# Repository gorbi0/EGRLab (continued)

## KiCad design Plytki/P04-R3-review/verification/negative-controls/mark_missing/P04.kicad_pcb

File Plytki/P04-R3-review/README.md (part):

# P04 SAFE — R3, schemat w formacie S1

*5.10.2026. Pakiet na kopii łańcucha schematu `P04-R2.2-review/src` według `Plytki/Format-S1/zadania/ZADANIE-P04-S1.md` (decyzja użytkownika 5.10.2026: wariant pełny, P04 na 6. poziomie, klasa L). Zamknięty pakiet R2.2 bez zmian.*

**Status (5.10.2026): schemat R3 i PCB (sesja lokalna, gałąź `p04-r3-pcb`) do recenzji; paczka zamówieniowa `Plytki/P04-PCB-R3-zamowienie`.** Sekcja „PCB” niżej. Sprzętu nie zmontowano ani nie zmierzono.

Obwód R2.2 zostaje: watchdog CD74HC123 (U1), zatrzask ARM 74HC74 (U3), regeneracja SAFE_N przez 74HC14 (U2), bramki 74HC08 (U4–U7), bufory 74LVC125AD z Ioff i podwójnymi pulldownami (U8–U10), nadzorca MCP100-300 (U11), otwarte kolektory Q1–Q3 na SAFE_N, druga droga watchdoga SAFE_WD, R17 10 kΩ pod reset z P03. Zmieniają się złącza do innych płytek, punkty pomiarowe, typy części i wymiar. `verify_s1.py` sprawdza na eksportowanej netliście, że poza złączami J1–J8 i polami TP każdy pin ma tę samą sieć i wartość co w R2.2 (`reference/P04-R2.2.xml`), z dwiema jawnymi zmianami nazw.

## Zmiany R2.2 → R3

| Punkt | R2.2 | R3 |
|---|---|---|
| Płytka | 160 × 120 mm, 4 otwory, samodzielna | klasa L 160 × 100 mm, poziom 6 (sloty S1–S3), 12 otworów M3, dystanse 20 mm |
| Złącza | J1 LV04 i J2 SAFE (pigtaile z kotwami), J3–J6 IDC, J7 PG i J8 PANELSAFE (Mini-Fit) | **J_BP1** IDC 2×8 (S1, x = 26,5), **J_BP2** i **J_BP3** IDC 2×10 (S2 x = 80,0, S3 x = 133,5), kątowe obudowane, wszystkie nieparzyste GND, przez P12 |
| Nazwy sieci | SUP_N (J2.15), PG_3V3 (J7.1) | **SUP_N_OUT**, **P04_3V3** — nazwy z P12 (P03 R6 J_BP3.12, P02 R4 J_BP.15) |
| Drugi koniec PG/SAFE_N | P01 J5 | P02 R4 (Q7, zwora PG) przez P12; P07 łączy się z SAFE_N po nazwie |
| Punkty pomiarowe | TP1–TP15 | **J_SV1** 1×13, **J_SV2** 1×7, **J_SV3** 1×7 na krawędzi B; 19 kołków przez R43–R61 przy węzłach (mapa w `docs/ODBIOR.md`) |
| Rezystory | MFR-25 THT leżące | nowe **SMD 1206** RC1206FR-07… (rejestr nie ma zapasu tych wartości) |
| Kondensatory | K104K15 100 n THT, K102J15 1 n, EEUFR1H100, 2 × MKS2 63 V | 100 n **X7R 1206**; posiadane: C1 MKS2 1 µF / 100 V, C3 EEU-EB1J100SH, C18 C320C102J1G5TA; C2 nowy MKS2 jak w R2.2 |
| U8–U10 | SO14 na adapterach Kamami, C15–C17 na adapterach | **SOIC-14 lutowane wprost** (S1 §9); C15–C17 na płytce jako druga 100 n przy U8–U10 |
| Arkusze | 6 (w tym `CON`) | 7: `CON` → **`ZLACZA`** (nazwa zarezerwowana w Windows, `docs/CHMURA.md`), nowy **`SERWIS`** |

## Pinout J_BP (pełny: `docs/J_BP.csv`, kierunki widziane z P04)

| Pin | J_BP1 (S1) | J_BP2 (S2) | J_BP3 (S3) |
|---|---|---|---|
| 2 | PANEL_3V3 → P11 | MOTOR_PERMIT → P07 | SENSOR_ENABLE ← P03 |
| 4 | MECH_OK ← P11 | PWM_OUT → P07 | CORE_LINK ← P03 |
| 6 | STOP_NC_OUT ← P11 | ARM_CLK → P07 | HW_ARMED → P03 |
| 8 | ARM_CONTACT ← P11 | DRIVE_OK ← P07 | 5V_SYS (tylko kołek) |
| 10 | SENSOR_PERMIT → P08 | 3V3_IO (zasilanie) | 3V3_IO (zasilanie) |
| 12 | SENSOR_OK ← P08 | PSU_OK ← P02 | SUP_N_OUT ← P03 |
| 14 | TEST_KEY ← P11 | P04_3V3 → P02 | PWM ← P03 |
| 16 | DAQ_OK ← P05 | SAFE_N (węzeł OC) | HEARTBEAT ← P03 |
| 18 | — | PG_LINK (pętla P02) | MCU_ARM ← P03 |
| 20 | — | PG_SEND (pętla P02) | INTERLOCK → P03 |

Nieparzyste: GND. Te same numery pinów co u partnera tam, gdzie się dało: J_BP1 2/4/6/8/14 = P11 J_P12, J_BP2 12/16/18 = P02 R4 J_BP, J_BP3 12–20 = P03 R6 J_BP3 — taśmy na P12 idą wtedy prosto. Sieci do P07 (DRIVE) i P08 (SENSOR) mają nazwy z R2.2 J3/J4 (i z P08 R1 W2); **P07 jeszcze nie istnieje — te sieci czekają na P07**.

## Kontrole

`python src/run_schematic.py` (w chmurze `scripts/egrlab-docker python3 src/run_schematic.py`, ok. 20 s): schemat, tabele, ERC, netlista, cztery zestawy kontroli, PDF, `verification/QA.md`, manifest.

- ERC **0** na 7 arkuszach; netlista **397/397** pinów zgodnych z `parts.py`, 100 części, 95 sieci.
- `verify_electrical.py` (kontrole R2.2 z pinami przeniesionymi na J_BP): **22/22**, mutacje **16/16** — m.in. pełne tabele prawdy INTERLOCK / SAFE_N / HW_ARMED / MOTOR_PERMIT / PWM_OUT / SENSOR_PERMIT (131 072 wierszy), druga droga watchdoga bez Q1, sekwencje ARM bez samoczynnego uzbrojenia, SAFE_N tylko z jednym podciąganiem i kolektorami (rezystor kołka serwisowego pominięty jawnie), 3V3 wychodzi z płytki tylko przez R38/R39/R40.
- `verify_values.py`: **10/10**, mutacje **24/24** (wartości i MPN S1, rogi rezystorów panelu i SAFE_N).
- `verify_reset.py` z mapą części **P03 R6**: **7/7**, mutacje **4/4** (R17 10 kΩ, VIL/VIH na U9.5, SUP_N_OUT na J_BP3.12 po obu stronach).
- `verify_s1.py` (kontrakt S1 i P12, niezależny od generatora): **34/34**, mutacje **42/42** wykryte przez kontrolę docelową, próba zerowa czysta. Sprawdza m.in.: pinout i footprint każdego J_BP; nieparzyste GND; każda sieć dawnych J1–J8 na J_BP dokładnie raz (3V3_IO dwa razy); te same piny co partner; **każda z 19 sieci „czeka na P04” w `reference/P12-kontrakty.json` kończy się na P04 dokładnie raz i po dołączeniu P04 ma jeden nadajnik (albo pętlę)**; brak obcych nazw; nazwy DRIVE/SENSOR jak w R2.2 i P08 R1; zgodność `J_BP.csv` i `SERWIS.csv` z netlistą; listwy ≤ 13 kołków z GND na końcach, rezystor przy węźle w swojej klasie, SAFE_N i ARM_BUTTON_N tylko obok GND, szyny tylko obok GND lub szyn; pokrycie TP1–TP15 z R2.2; obudowy S1; obwód R2.2 bez zmian.
- kicad-cli wypisuje „schemat posiada błędy numeracji” — oznaczenia `J_BP1…3`, `J_SV1…3` (nazwy formatu S1); ERC tego nie zgłasza.

## Decyzje (sporne oznaczone)

1. **Trzy J_BP zamiast dwóch z budżetu S1 §8:** 25 sygnałów (19 czekających na P04 w P12 + 6 do P07/P08) i zasilanie nie mieszczą się w 2 × 10 parzystych pinach bez wyjątków od GND na nieparzystych; klasa L ma trzy sloty. J_BP1 jako 2×8 (osiem sygnałów).
2. **Sporne — SAFE_N w `J_BP.csv` jako `in`:** P04 ma podciąganie R4 i własne kolektory Q1–Q3, ale dla kontraktu P12 nadajnikiem jest P02 R4 (`out`); dwa `out` kontrola P12 uznałaby za konflikt. Uwaga w kolumnie `uwagi`.
3. **Sporne — U8–U10 SOIC wprost, bez adapterów:** S1 §9 dopuszcza adaptery tylko tam, gdzie jest miejsce; SOIC na płytce z fabryki jest prostszy i niższy (tak samo P06 R2). Adaptery z przydziału P04 zostają w rejestrze. C15–C17 przeniesione na płytkę, żeby obwód był identyczny z R2.2 — mogą zostać DNP.
4. **5V_SYS na jednym pinie (J_BP3.8), tylko do kołka J_SV3.2** — jak J1.1 → TP13 w R2.2; P04 nie pobiera 5 V, więc reguła „5V_SYS na ≥ 2 pinach” (S1 §5, dla zasilania) nie ma tu zastosowania.
5. **3V3_IO na dwóch pinach (J_BP2.10, J_BP3.10):** pobór kilka–kilkanaście mA, ale drugi pin daje zapas styku i masę obok.
6. **Klasy rezystorów kołków:** 1 kΩ szyny i węzły napędzane bramką; 10 kΩ węzły pasywne SAFE_N (R4 10k / R5 100k) i ARM_BUTTON_N (R2 10k). **Wyjątek Q1_B 1 kΩ:** próba E21 zwiera kołek do GND i musi zatkać Q1 (z 10 kΩ baza zostaje na ok. 1,57 V, z 1 kΩ ok. 0,30 V). **SAFE_N i ARM_BUTTON_N stoją tylko między kołkami GND:** zsunięta sonda zwierająca je z szyną podniosłaby SAFE_N mimo otwartego STOP albo dała zbocze ARM.
7. **Posiadane ostatnie sztuki z rejestru:** C1 MKS2 1 µF / 100 V (5 %), C3 EEU-EB1J100SH, C18 C320C102J1G5TA — bilans w `docs/ZAKUPY.md`. C2 zostaje foliowy (nowy, jak w R2.2), bo filtr ARM i tak wymaga kwalifikacji przycisku.

## PCB (5.10.2026, sesja lokalna; `src/run_release.py`, KiCad 10.0.6 w Dockerze)

| Kontrola | Wynik | Raport |
|---|---|---|
| DRC świeży, wszystkie poziomy, z parity | 0 niepołączonych, 0 niezgodności ze schematem, 0 innych naruszeń; 6 × `lib_footprint_mismatch` (J_BP1–3, J_SV1–3: nadruk przycięty przez `silkscreen.py`, pola równe bibliotece — przyjęte jawnie) | `verification/drc.json` |
| Kontrole PCB (`verify_pcb.py`) | 31/31 | `verification/pcb-checks.json`, `QA-PCB.md` |
| Próby ujemne PCB | 33/33 z próbą zerową | `verification/negative-controls.json` |
| Otwory M3 i strefy Ø7 | 12 NPTH 3,2 mm w punktach S1, bez miedzi i części w Ø7 | `pcb-checks.json` |
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
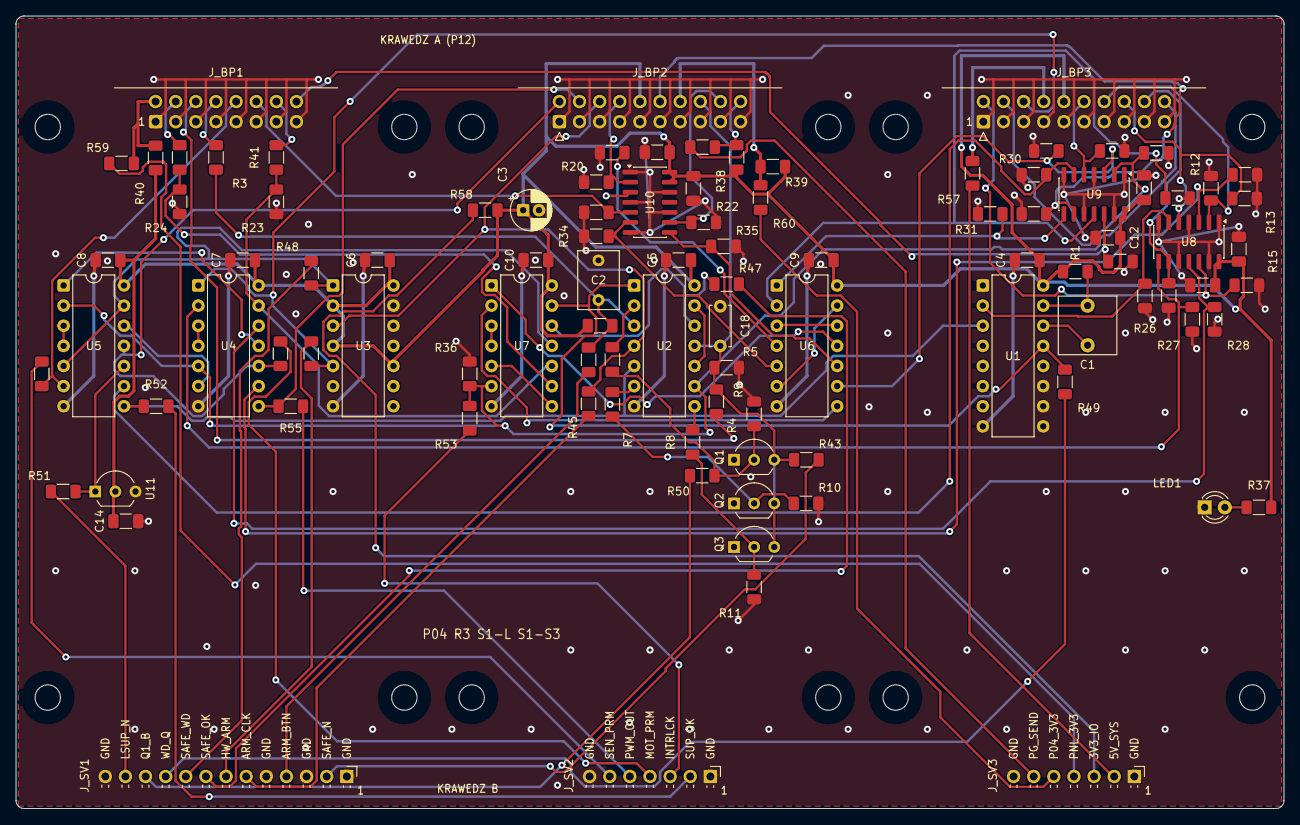
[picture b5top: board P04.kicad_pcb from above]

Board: 2 copper layers, 160.0 x 100.0 mm, 112 parts (0 on the bottom side), 86 nets.

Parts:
C1: 1u; C_WIMA_MKS2_1u100V_L7.2_W7.2_P5
C2: 1u; C_Rect_L7.2mm_W5.0mm_P5.00mm
C3: 10u; CP_Radial_D5.0mm_P2.00mm
C4, C5, C6, C7, C8, C9, C10, C11, C12, C13, C14, C15, C16, C17: 100n; C_1206_3216Metric_Pad1.33x1.80mm_HandSolder
C18: 1n; C_Disc_D5.0mm_W2.5mm_P5.00mm
H1, H2, H3, H4, H5, H6, H7, H8, H9, H10, H11, H12: M3 NPTH
J_BP1: J_BP1; IDC-Header_2x08_P2.54mm_Horizontal
J_BP2: J_BP2; IDC-Header_2x10_P2.54mm_Horizontal
J_BP3: J_BP3; IDC-Header_2x10_P2.54mm_Horizontal
J_SV1: J_SV1 SERWIS 1x13; PinHeader_1x13_P2.54mm_Horizontal
J_SV2: J_SV2 SERWIS 1x7; PinHeader_1x07_P2.54mm_Horizontal
J_SV3: J_SV3 SERWIS 1x7; PinHeader_1x07_P2.54mm_Horizontal
LED1: POWER; LED_D3.0mm
Q1, Q2, Q3: 2N3904; TO-92_Inline_Wide
R1: 220K; R_1206_3216Metric_Pad1.30x1.75mm_HandSolder
R2, R4, R6, R7, R8, R12, R13, R14, R15, R16, R17, R18, R19, R20, R21, R22, R23, R24, R25, R29, R31, R32, R33, R34, R35, R36, R43, R44: 10K; R_1206_3216Metric_Pad1.30x1.75mm_HandSolder
R3, R37, R38, R39, R41, R42, R45, R46, R47, R48, R49, R50, R51, R52, R53, R54, R55, R56, R57, R58, R59, R60, R61: 1K; R_1206_3216Metric_Pad1.30x1.75mm_HandSolder
R5, R9, R10, R11, R28, R30: 100K; R_1206_3216Metric_Pad1.30x1.75mm_HandSolder
R26, R27: 47K; R_1206_3216Metric_Pad1.30x1.75mm_HandSolder
R40: 100R; R_1206_3216Metric_Pad1.30x1.75mm_HandSolder
U1: CD74HC123E; DIP-16_W7.62mm
U2: SN74HC14N; DIP-14_W7.62mm
U3: SN74HC74N; DIP-14_W7.62mm
U4, U5, U6, U7: SN74HC08N; DIP-14_W7.62mm
U8, U9, U10: 74LVC125AD; SOIC-14_3.9x8.7mm_P1.27mm
U11: MCP100-300DI/TO; TO-92_Inline_Wide

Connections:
3V3_IO: C3.1, C4.1, C5.1, C6.1, C7.1, C8.1, C9.1, C10.1, C11.1, C12.1, C13.1, C14.1, C15.1, C16.1, C17.1, J_BP2.10, J_BP3.10, R1.1, R2.1, R37.1, R38.1, R39.1, R40.1, R58.1, U1.16, U2.14, U3.2, U3.4, U3.10, U3.14, U4.14, U5.14, U6.14, U7.14, U8.14, U9.14, U10.13, U10.14, U11.2
5V_SYS: J_BP3.8, R57.1
/ILK/MECH_KEY: U7.5, U7.8
/ILK/MECH_OK_P04: R24.1, R42.2, U7.9
/ILK/MODULES_OK: U7.3, U7.4
/ILK/OK_A: U6.3, U6.12
/ILK/OK_AB: U6.11, U7.1
/ILK/OK_B: U6.6, U6.13
/ILK/OK_C: U6.8, U7.2
/LED_PWR: LED1.2, R37.2
/OUT/ARM_BOTH: U4.3, U4.4
/OUT/MOTOR_REQ: U4.6, U5.12
/OUT/SENSOR_INTERLOCK: U5.3, U5.4
/OUT/SENSOR_KEY: U4.11, U5.1
/SERWIS/SRV_3V3_IO: J_SV3.3, R58.2
/SERWIS/SRV_5V_SYS: J_SV3.2, R57.2
/SERWIS/SRV_ARM_BUTTON_N: J_SV1.4, R44.2
/SERWIS/SRV_ARM_CLK: J_SV1.6, R45.2
/SERWIS/SRV_HW_ARMED: J_SV1.7, R46.2
/SERWIS/SRV_INTERLOCK: J_SV2.3, R53.2
/SERWIS/SRV_LOCAL_SUP_N: J_SV1.12, R51.2
/SERWIS/SRV_MOTOR_PERMIT: J_SV2.4, R54.2
/SERWIS/SRV_P04_3V3: J_SV3.5, R60.2
/SERWIS/SRV_PANEL_3V3: J_SV3.4, R59.2
/SERWIS/SRV_PG_SEND: J_SV3.6, R61.2
/SERWIS/SRV_PWM_OUT: J_SV2.5, R55.2
/SERWIS/SRV_Q1_B: J_SV1.11, R50.2
/SERWIS/SRV_SAFE_N: J_SV1.2, R43.2
/SERWIS/SRV_SAFE_OK: J_SV1.8, R47.2
/SERWIS/SRV_SAFE_WD: J_SV1.9, R48.2
/SERWIS/SRV_SENSOR_PERMIT: J_SV2.6, R56.2
/SERWIS/SRV_SUP_OK: J_SV2.2, R52.2
/SERWIS/SRV_WD_Q: J_SV1.10, R49.2
/WD/ILK_BAD: R8.1, U2.8
/WD/Q2_B: Q2.2, R7.2, R10.1
/WD/Q3_B: Q3.2, R8.2, R11.1
/WD/SAFE_OK_N: U2.10, U2.13
/WD/SUP_BAD: R7.1, U2.6
/WD/WD_BAD: R6.1, U2.2
/WD/WD_C: C1.2, U1.14
/WD/WD_RC: C1.1, R1.2, U1.15
ARM_BUTTON_N: C2.1, R2.2, R3.1, R44.1, U2.3
ARM_CLK: J_BP2.6, R45.1, U2.4, U3.3
ARM_CONTACT: J_BP1.8, R3.2
CORE_LINK: J_BP3.4, R16.1, U9.2
CORE_LINK_P04: R29.1, U6.9, U9.3
DAQ_OK: J_BP1.16, R19.1, U9.12
DAQ_OK_P04: R32.1, U6.2, U9.11
DRIVE_OK: J_BP2.8, R20.1, U10.2
DRIVE_OK_P04: R33.1, U6.4, U10.3
GND: C2.2, C3.2, C4.2, C5.2, C6.2, C7.2, C8.2, C9.2, C10.2, C11.2, C12.2, C13.2, C14.2, C15.2, C16.2, C17.2, C18.2, J_BP1.1, J_BP1.3, J_BP1.5, J_BP1.7, J_BP1.9, J_BP1.11, J_BP1.13, J_BP1.15, J_BP2.1, J_BP2.3, J_BP2.5, J_BP2.7, J_BP2.9, J_BP2.11, J_BP2.13, J_BP2.15, J_BP2.17, J_BP2.19, J_BP3.1, J_BP3.3, J_BP3.5, J_BP3.7, J_BP3.9, J_BP3.11, J_BP3.13, J_BP3.15, J_BP3.17, J_BP3.19, J_SV1.1, J_SV1.3, J_SV1.5, J_SV1.13, J_SV2.1, J_SV2.7, J_SV3.1, J_SV3.7, LED1.1, Q1.1, Q2.1, Q3.1, R5.2, R9.2, R10.2, R11.2, R12.2, R13.2, R14.2, R15.2, R16.2, R17.2, R18.2, R19.2, R20.2, R21.2, R22.2, R23.2, R24.2, R25.2, R26.2, R27.2, R28.2, R29.2, R30.2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
HEARTBEAT: J_BP3.16, R13.1, U8.5
HEARTBEAT_P04: R26.1, U1.2, U8.6
HW_ARMED: J_BP3.6, R46.1, U3.5, U4.1
INTERLOCK: J_BP3.20, R36.1, R53.1, U2.9, U4.5, U5.2, U7.6
LOCAL_SUP_N: R51.1, U5.10, U11.1
MCU_ARM: J_BP3.18, R14.1, U8.9
MCU_ARM_P04: R27.1, U4.2, U8.8
MECH_OK: J_BP1.4, R42.1
MOTOR_PERMIT: J_BP2.2, R54.1, U4.10, U5.11
P04_3V3: J_BP2.14, R39.2, R60.1
PANEL_3V3: J_BP1.2, R40.2, R59.1
PG_LINK: J_BP2.18, R22.1, U10.9
PG_LINK_P04: R35.1, U6.10, U10.8
PG_SEND: J_BP2.20, R38.2, R61.1
PSU_OK: J_BP2.12, R18.1, U9.9
PSU_OK_P04: R31.1, U6.1, U9.8
PWM: J_BP3.14, R12.1, U8.2
PWM_OUT: J_BP2.4, R55.1, U4.8
PWM_P04: R25.1, U4.9, U8.3
Q1_B: Q1.2, R6.2, R9.1, R50.1
SAFE_N: C18.1, J_BP2.16, Q1.3, Q2.3, Q3.3, R4.2, R5.1, R43.1, U2.11
SAFE_OK: R47.1, U2.12, U7.12
SAFE_WD: R48.1, U3.1, U5.5, U5.13, U7.11
SENSOR_ENABLE: J_BP3.2, R15.1, U8.12
SENSOR_ENABLE_P04: R28.1, U4.12, U8.11
SENSOR_OK: J_BP1.12, R21.1, U10.5
SENSOR_OK_P04: R34.1, U6.5, U10.6
SENSOR_PERMIT: J_BP1.10, R56.1, U5.6
STOP_NC_OUT: J_BP1.6, R4.1
SUP_N_OUT: J_BP3.12, R17.1, U9.5
SUP_N_P04: R30.1, U5.9, U9.6
SUP_OK: R52.1, U1.3, U2.5, U5.8
TEST_KEY: J_BP1.14, R41.1
TEST_KEY_P04: R23.1, R41.2, U4.13, U7.10
WD_Q: R49.1, U1.13, U2.1, U7.13

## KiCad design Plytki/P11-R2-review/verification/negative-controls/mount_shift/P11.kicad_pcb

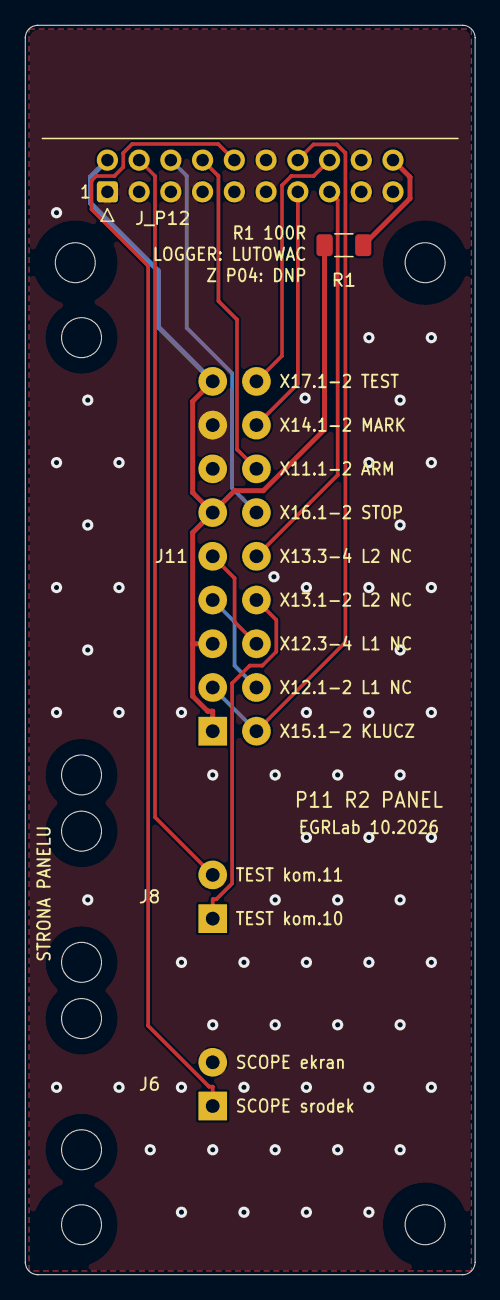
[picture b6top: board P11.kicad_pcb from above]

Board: 2 copper layers, 36.0 x 100.0 mm, 9 parts (0 on the bottom side), 14 nets.

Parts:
H1, H2, H3, H4: M3 NPTH
J6: SCOPE tail; FIELD_PAIR2
J8: TEST signal; FIELD_PAIR2
J11: CONTACTS; FIELD_CONTACT18
J_P12: IDC 2x10 katowe do P12; IDC-Header_2x10_P2.54mm_Horizontal
R1: 100R; R_1206_3216Metric_Pad1.30x1.75mm_HandSolder

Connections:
/3V3_IO: J_P12.20, R1.1
/CONTACTS/DIAG_L1_L2: J11.6, J11.9
/CONTACTS/ILK_L1_L2: J11.4, J11.7
/CONTACTS/LOOP_OUT: J8.1, J11.8
/N_J_SCOPE_HOT: J6.1, J_P12.10
ARM_CONTACT: J11.14, J_P12.8
GND: J6.2, J11.13, J11.15, J_P12.1, J_P12.3, J_P12.5, J_P12.7, J_P12.9, J_P12.11, J_P12.12, J_P12.17, J_P12.18, J_P12.19
LOGGER_CLEAR: J11.10, J_P12.15
MARK: J11.16, J_P12.13
MECH_OK: J8.2, J_P12.4
PANEL_3V3: J11.1, J11.5, J11.11, J11.17, J_P12.2, R1.2
STOP_NC_OUT: J11.12, J_P12.6
TEST_KEY: J11.2, J11.3, J_P12.14
TEST_PRESENT: J11.18, J_P12.16

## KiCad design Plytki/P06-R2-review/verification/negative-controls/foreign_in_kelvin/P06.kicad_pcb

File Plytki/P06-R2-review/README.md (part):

# P06 I-LOGGER — R2, schemat w formacie S1

*1.10.2026. Pakiet na kopii łańcucha `P06-R1-review/src` według `Plytki/Format-S1/zadania/ZADANIE-P06-S1.md` (decyzje użytkownika 1.10.2026: klasa 2/3, bocznik 2512 Kelvin, BYPASS na panelu, C3 220 µF). Zamknięty pakiet R1 bez zmian.*

**Status: schemat R2 po przeglądzie lokalnym, PCB R2 po recenzji niezależnej i poprawkach (2.10)** — sekcja „PCB” niżej. Sprzętu nie zmontowano ani nie zmierzono.

Obwód R1 zostaje: INA240A2 z filtrem R1/R2 10 Ω, dzielnik R3/R4 1:2, MCP6022, MCP3201, nadzorcy MCP120, bufory 74LVC125 z Ioff, logika LOGGER_CURRENT_OK, R21 (prąd zwilżania styku statusu BYPASS). Zmieniają się złącza do innych płytek, bocznik, punkty pomiarowe i typy części. `verify_s1.py` sprawdza na eksportowanej netliście, że poza J1/J2, bocznikiem i polami testowymi każdy pin obwodu R1 ma tę samą sieć co w R1 (`reference/P06-R1.xml`).

## Zmiany R1 → R2

| Punkt | R1 | R2 |
|---|---|---|
| Płytka | 120 × 100 mm, 2 × 70 µm, samodzielnie mocowana | klasa 2/3, 106,5 × 100 mm, sloty S1–S2 poziomu 4, dystanse 20 mm, 35 µm |
| Zasilanie i ILOG | J1 LV06 (Mini-Fit 4p, 200 mm) i J2 ILOG (taśma 8 żył do P03) | **J_BP** IDC 2×8 kątowe, slot S2 (x = 80,0 mm): ADC_SCLK 2, ADC_DOUTA 4 (jak J_BP2 płytek P03 R6 i P05 R3), CS_ILOG_N 6, LOGGER_CURRENT_OK 8, 5V_SYS 10 i 12, 3V3_IO 14, nieparzyste i 16 GND |
| Przewody | 5 wiązek | zostają J3 ISERIES, J4 BYPASS (tor mocy), J5 status BYPASS — przy brzegu x = 0 |
| Bocznik RSH1 | PBV-R005-F1-0.5 THT, 3 W | **SMD 2512 Kelvin 5 mΩ 1 %**, Vishay **WSK25125L000FEA**, footprint lokalny `P06:R_Shunt_Vishay_WSK2512_T1.19mm_SenseE1.70` (pady 1/4 prądowe, 2/3 pomiarowe; przegląd 1.10) |
| SW1 BYPASS | NKK S6A | ogólny **DPDT ON-ON ≥ 10 A DC** z oczkami, na panelu; MPN do potwierdzenia |
| Punkty pomiarowe | TP1–TP15 | **J_SV1** 1×7 (S1: węzły analogowe przez 10 kΩ) i **J_SV2** 1×13 (S2: szyny i logika); 14 kołków przez rezystory przy węźle R25–R38 |
| R3/R4 | 5,1 kΩ 0,1 % THT | **5,11 kΩ 0,1 % 1206, 25 ppm/K** (zamiana 1:1 z listy 2); dzielnik 1:2 bez zmian, obciążenie INA240 10,22 kΩ |
| C3 | 470 µF / 16 V D8 | **220 µF / 16 V** D6,3 (decyzja 1.10); impuls ładowania przez R6 ok. 3,0 mJ (było 6,5 mJ) |
| C1 | 470 nF PET | 470 nF X7R 1206 (τ nominalnie 1,201 ms, 132,5 Hz; z tolerancją X7R 0,92–1,39 ms) |
| C4/C5 | 4,7 µF elektrolit D5 | 4,7 µF X7R 1206 25 V (MCP1525: CL 1–10 µF; MCP1702: ceramika X7R) |
| R i C | THT DIN0207, 0805 | nowe **SMD 1206**; R11 47 kΩ z rejestru (MF0207 na stojąco) — `docs/ZAKUPY.md` |
| Arkusze | 6 | 7 (CONNECT: J_BP; nowy SERWIS: listwy) |

**Wyjątki od „nowe = SMD 1206” (S1 §1/§9):**
- **RSH1** 2512 z czterema polami — tor 5–6 A i pomiar Kelvina (decyzja 28.09/1.10).
- **R6** 1 Ω / 1 W KNP01U-1R leżący (DIN0411) — rezystor mocy jak R1 w P05 R3; impuls ładowania C3 ok. 3 mJ, a posiadany MF0207 1R ma 0,6 W.
- **R21** 39 Ω PR02 2 W leżący (footprint `R_PR02_P17.78` z P02 R4). Wydziela 0,64 W przy 5,00 V i 0,71 W przy 5,25 V. W 2512 1 W pracowałby na ok. 70 % mocy z gorącym punktem na laminacie obok toru analogowego; PR02 ma 36 % obciążenia i stoi 3–5 mm nad płytką. 2512 2 W to część specjalna. **Decyzja użytkownika 1.10: zostaje THT (PR02).**
- **C3** elektrolit radialny 220 µF.
- **D1** 1N5819 (DO-41) i **D2** BAT85 (DO-35), układy scalone — obudowy jak w R1 (SOIC tylko od góry).

## Kontrole

`python src/run_schematic.py` (Python KiCada; w chmurze `scripts/egrlab-docker python3 src/run_schematic.py`, ok. 17 s): schemat, tabele, ERC, netlista, trzy zestawy kontroli, PDF, `verification/QA.md`, manifest.

- ERC **0** na 7 arkuszach; netlista **243/243** pinów zgodnych z `parts.py`, 74 części, 54 sieci (1.10 po przeglądzie lokalnym: J3 bez pustych pól 3/4) (R1: 6 arkuszy, 70 części).
- `verify_electrical.py` (kontrole R1 dostosowane): **33/33**, mutacje **30/30** — m.in. J_BP i dojście każdego sygnału do tego samego elementu co w R1, dzielnik 5,11 kΩ 0,1 %, C5/C4 z obniżeniem X7R (C5 efektywnie 2,5–5,9 µF w oknie 1–10 µF), C3 220 µF, R6 1 W, R21 2 W ≥ 2 × moc, 3V3_IO tylko do J_BP i kołka, tabela prawdy READY z eksportu.
- `verify_s1.py` (kontrakt S1, niezależny od generatora): **27/27**, mutacje **37/37** wykryte przez kontrolę docelową, próba zerowa czysta. Pinout J_BP dokładnie jak w zadaniu; ADC_SCLK/ADC_DOUTA na pinach 2/4 jak J_BP2 w `reference/P03-R6-J_BP.csv` (gałąź `p03-r6-pcb`, b094fa7) i `reference/P05-R3-J_BP.csv`; kierunki w `J_BP.csv` przeciwne do P03 R6; każda sieć dawnych J1/J2 na J_BP dokładnie raz (5V_SYS dwa razy); nieparzyste piny GND; J3/J4/J5 i Kelvin poza J_BP; listwy ≤ 13 kołków, GND na końcach, rezystor przy węźle w klasie z S1 §6, zasada sąsiedztwa szyn, pokrycie TP1–TP15 z R1; `J_BP.csv`/`SERWIS.csv` zgodne z netlistą; RSH1: 4 pola, pola prądowe (dwa największe) ECU_P1/EGR_P1, pomiarowe K_PLUS/K_MINUS po tej samej stronie — z geometrii footprintu; C3 220 µF; źródła i obudowy części; obwód R1 bez zmian.
- kicad-cli wypisuje „schemat posiada błędy numeracji” — dotyczy oznaczenia `J_BP` bez numeru (nazwa z zadania, jak w P02 R4); ERC tego nie zgłasza.

## Listwy serwisowe (krawędź B)

| J_SV1 (S1, x = 10–43) | Sieć | Rezystor | J_SV2 (S2, x = 63,5–96,5) | Sieć | Rezystor |
|---|---|---|---|---|---|
| 1 | GND | — | 1 | GND | — |
| 2 | I_L_OUT | R25 10k | 2 | 5V_SYS | R29 1k |
| 3 | ADC_AIN | R26 10k | 3 | 5VA_P06 | R30 1k |
| 4 | GND | — | 4 | 3V3_P06 | R31 1k |
| 5 | REF_BUF | R27 10k | 5 | GND | — |
| 6 | REF25 | R28 10k | 6 | 3V3_IO | R32 1k |
| 7 | GND | — | 7 | SUP3_N | R33 10k |
| | | | 8 | SUP5_N | R34 10k |
| | | | 9 | SHUNT_ENABLED | R35 1k |
| | | | 10 | LOGGER_CURRENT_OK | R36 1k |
| | | | 11 | CS_LOCAL_N | R37 1k |
| | | | 12 | CLK_LOCAL | R38 1k |
| | | | 13 | GND | — |

Szyny stoją tylko obok GND, innej szyny albo linii za 10 kΩ, która nie jest węzłem analogowym (3V3_IO obok SUP3_N). Węzły analogowe są na osobnej listwie, poza sąsiedztwem szyn. I_L_OUT ma 10 kΩ, choć zadanie wymienia go tylko na liście węzłów: to wyjście INA240, a 10 kΩ odcina pojemność toru do kołka od wyjścia wzmacniacza (multimetr 10 MΩ: błąd 0,1 %). SUP5_N ma 10 kΩ według zadania, choć na P06 jest wyjściem bufora U6A (w P05 R3 analogiczny P05_SUP5_N ma 1 kΩ) — 10 kΩ nic nie psuje. Kolejność w listwie może zmienić layout: `src/parts.py` (listy SV1/SV2), potem `run_schematic.py`.

## Wymagania dla layoutu (sesja lokalna)

- **Strona panelu (x = 0):** J3 ISERIES, J4 BYPASS i J5 status BYPASS przy brzegu x = 0 (S1 §7: ISERIES najkrótszą drogą), pola PTH J3 i J4 tuż przy RSH1. Pigtaile jak w R1: otwory 2,4 mm / pady 4,5 mm dla 2,5 mm², 1,1 / 2,2 mm dla AWG22, dwa otwory kotwy 3,2 mm 12 mm od rzędu.
- **Tor 5–6 A na miedzi 35 µm (S1 §3):** od J3 przez pola prądowe RSH1 do J4 jako pola ≥ 4 mm szerokości na obu warstwach, zszyte przelotkami, możliwie krótko (R1: 6 mm / 70 µm). Bez przelotek w samym polu RSH1 i bez innych sieci pod bocznikiem.
- **Kelvin:** ścieżki od pól pomiarowych 2/3 RSH1 do R1/R2 i dalej do U1.8/U1.1 osobno, parą, z dala od toru mocy i R21; R1/R2 i U1 blisko bocznika. Żadnego złącza między Kelvinem a INA240.
- **J_BP** w slocie S2, środek x = 80,0 mm, pin 1 od strony mniejszego x, strona wtyku równo z krawędzią A; pas y = 0–10 mm tylko na długości złącza.
- **J_SV1** w x = 10–43 mm, **J_SV2** w x = 63,5–96,5 mm, kątowe, kołki ok. 6 mm za krawędzią B; rezystory R25–R38 **przy węzłach** (SMD, mogą być od spodu). Nadruk: nazwa sieci przy każdym kołku, czytelna od strony B.
- **Poziom 4:** od góry ≤ 16,5 mm (najwyższe: C3 ok. 11,2 mm, U2/U3 w podstawkach ok. 8 mm, R21 leżący ok. 9 mm z odstępem); **od spodu tylko SMD ≤ 1,5 mm, bez SOIC** (U1, U5, U6 od góry); wyprowadzenia THT przycięte do ≤ 1,5 mm. Osiem otworów M3 (x = 4,0 / 49,0 / 57,5 / 102,5; y = 14,0 / 86,0), strefa Ø 7 mm.
- **R21** odsunięty od RSH1, U1 i U10 (gorący element); nad nim nie prowadzić taśmy.
- Szczegóły: `docs/MECHANIKA.md`.

## PCB (1.10.2026, poprawki po recenzji 2.10.2026; `src/run_release.py`, KiCad 10.0.6 w Dockerze)

| Kontrola | Wynik | Raport |
|---|---|---|
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
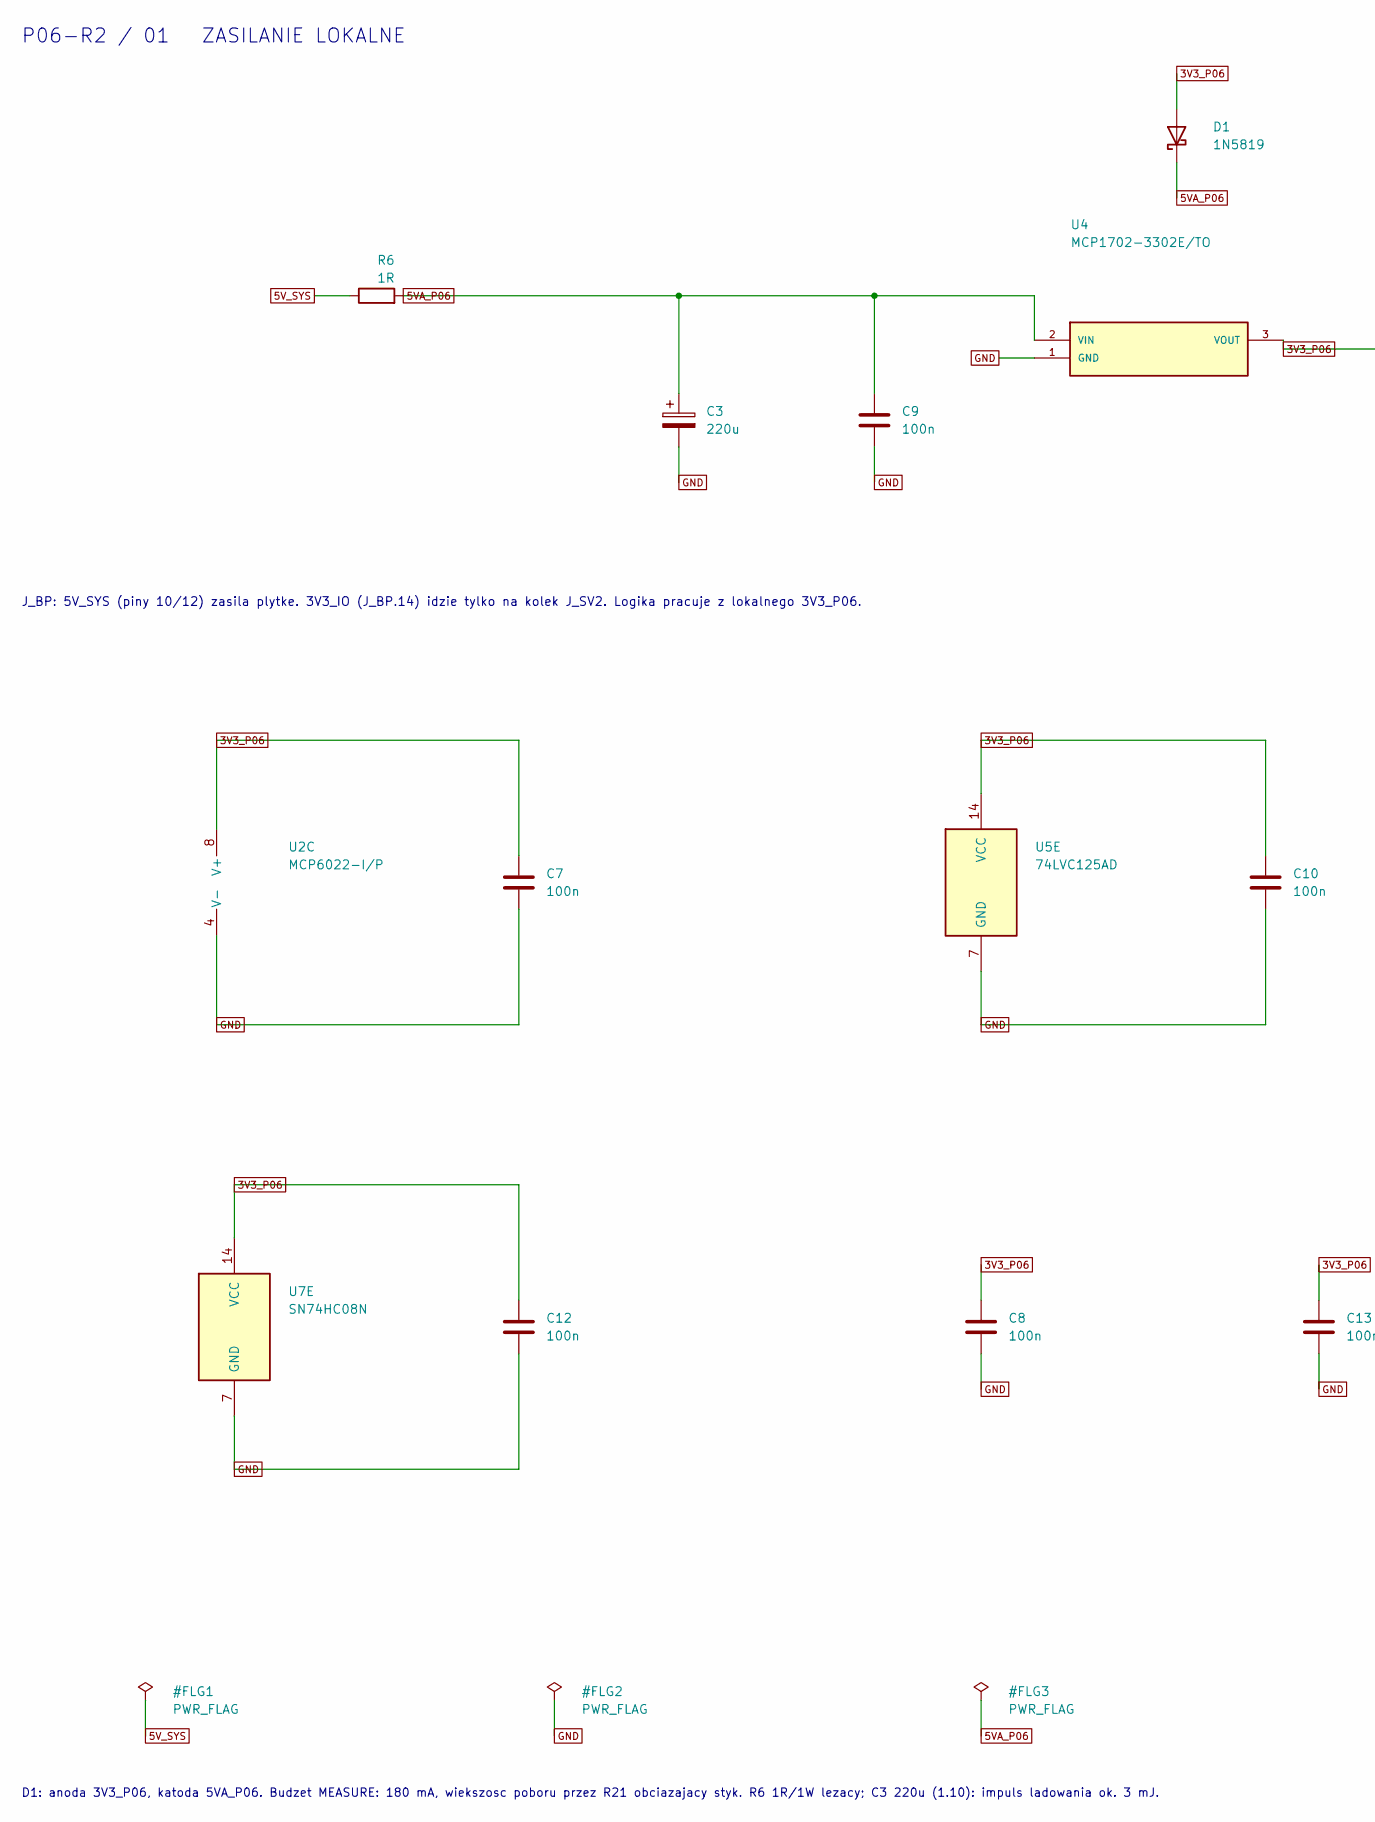
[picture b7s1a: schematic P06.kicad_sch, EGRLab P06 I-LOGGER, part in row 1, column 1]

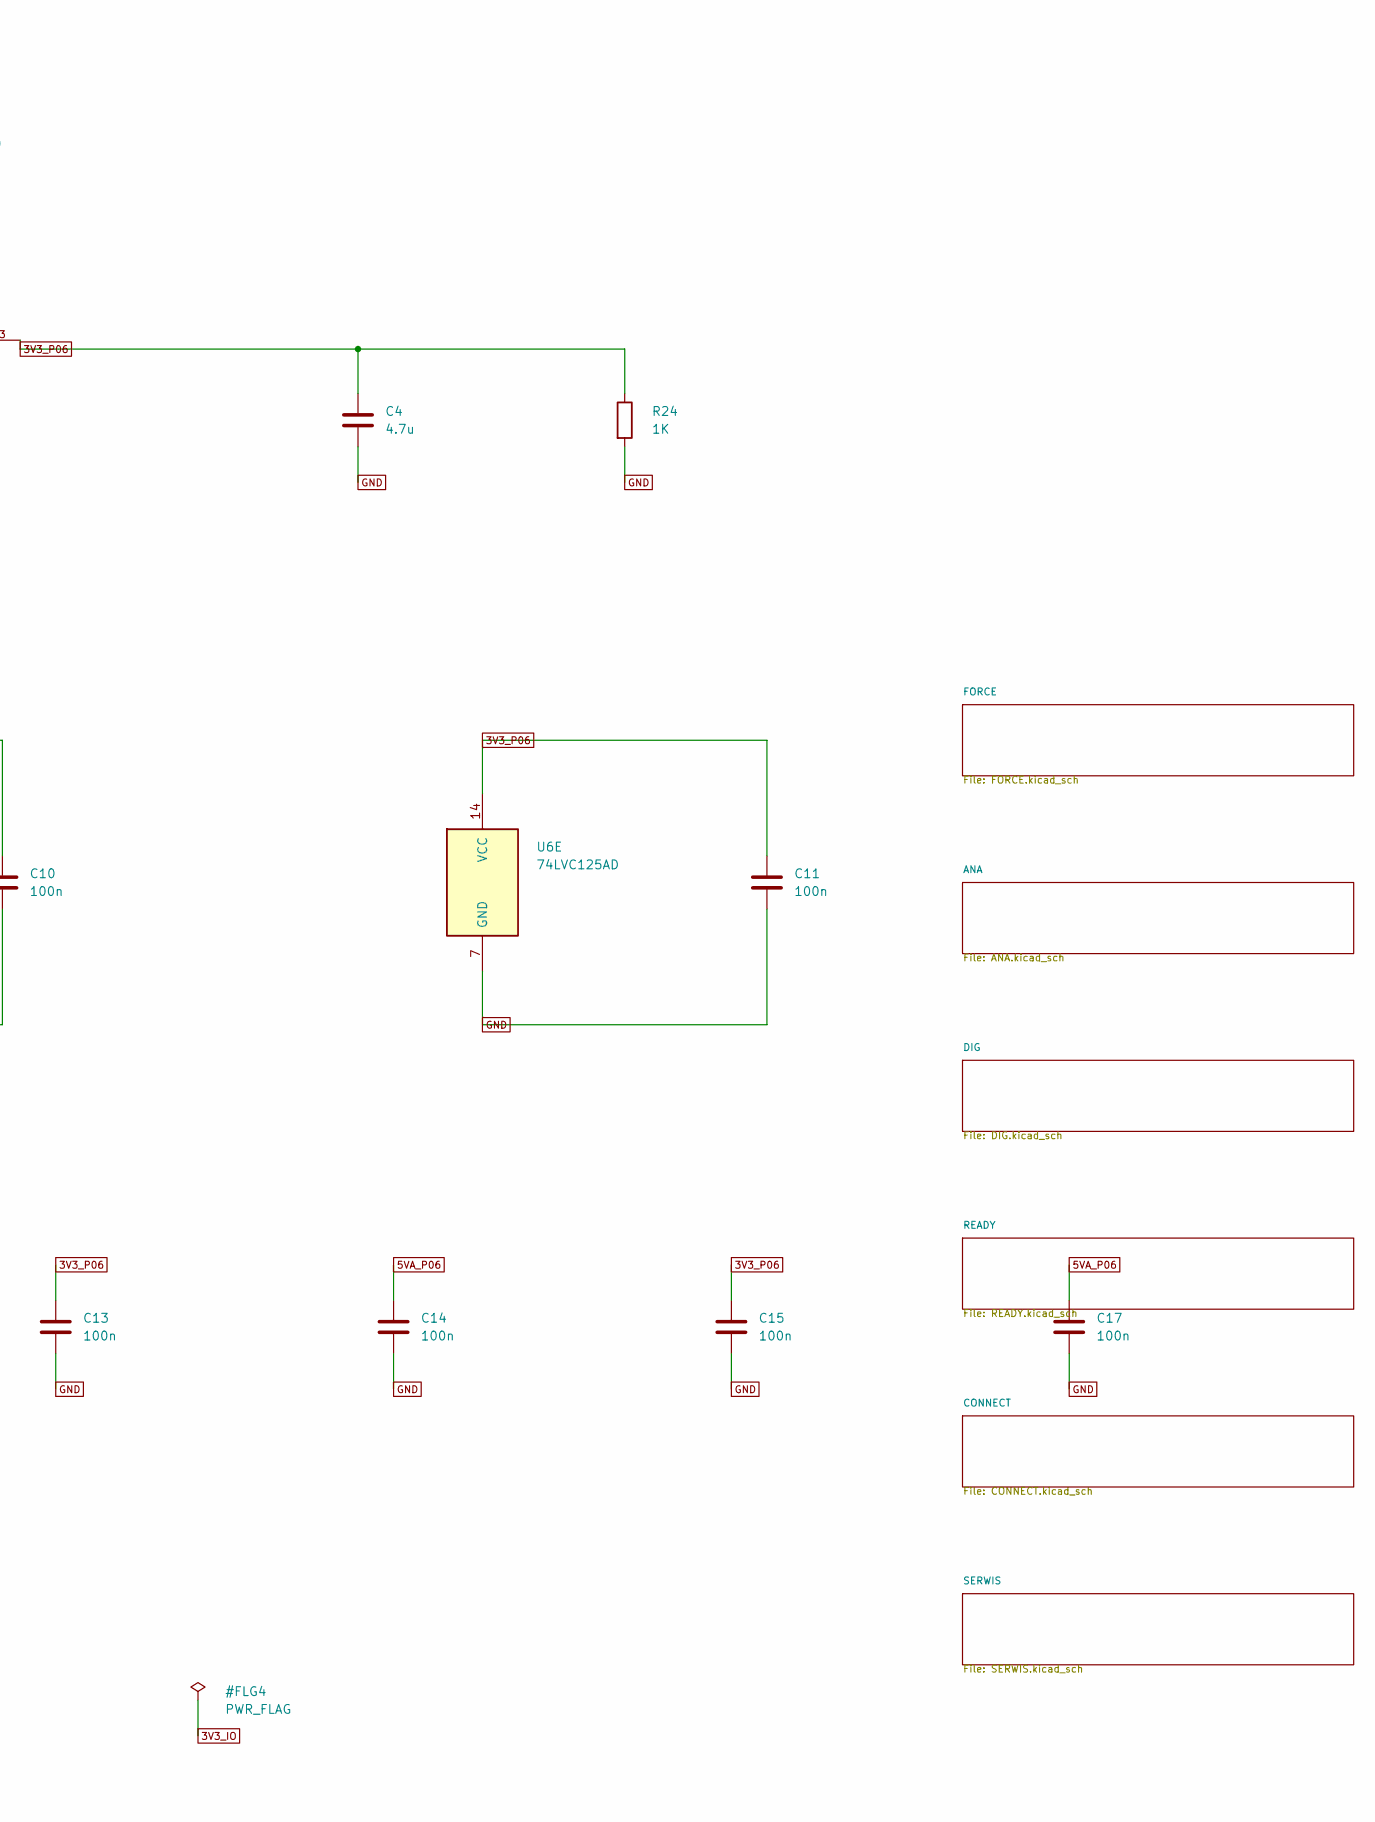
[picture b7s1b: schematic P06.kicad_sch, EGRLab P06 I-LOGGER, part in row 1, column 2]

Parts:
C3: 220u; CP_Radial_D6.3mm_P2.50mm; MPN EEUFR1C221
C4: 4.7u; C_1206_3216Metric_Pad1.33x1.80mm_HandSolder; MPN SMD 1206 X7R 25V 10% 4.7u
C7, C8, C9, C10, C11, C12, C13, C14, C15, C17: 100n; C_1206_3216Metric_Pad1.33x1.80mm_HandSolder; MPN SMD 1206 X7R 50V 10% 100n
D1: 1N5819; D_DO-41_SOD81_P10.16mm_Horizontal; MPN 1N5819
R6: 1R; R_Axial_DIN0411_L9.9mm_D3.6mm_P15.24mm_Horizontal; MPN KNP01U-1R (1R 1W wirewound, body 3x9mm)
R24: 1K; R_1206_3216Metric_Pad1.30x1.75mm_HandSolder; MPN RC1206FR-071KL
U2: MCP6022-I/P; DIP-8_W7.62mm; MPN MCP6022-I/P
U4: MCP1702-3302E/TO; TO-92_Inline_Wide; MPN MCP1702-3302E/TO
U5, U6: 74LVC125AD; SOIC-14_3.9x8.7mm_P1.27mm; MPN 74LVC125AD,118 (Nexperia)
U7: SN74HC08N; DIP-14_W7.62mm; MPN SN74HC08N

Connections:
3V3_P06: C4.1, C7.1, C8.1, C10.1, C11.1, C12.1, C13.1, C15.1, D1.2 (A), R24.1, U2.8 (V+), U4.3 (VOUT), U5.14 (VCC), U6.14 (VCC), U7.14 (VCC); also elsewhere on the board
5VA_P06: C3.1, C9.1, C14.1, C17.1, D1.1 (K), R6.2, U4.2 (VIN); also elsewhere on the board
5V_SYS: R6.1; also elsewhere on the board
/ANA/I_DIV: U2.3 (+); also elsewhere on the board
ADC_BUF: U2.1, U2.2 (-); also elsewhere on the board
GND: C3.2, C4.2, C7.2, C8.2, C9.2, C10.2, C11.2, C12.2, C13.2, C14.2, C15.2, C17.2, R24.2, U2.4 (V-), U4.1 (GND), U5.7 (GND), U6.7 (GND), U7.7 (GND); also elsewhere on the board
REF25: U2.5 (+); also elsewhere on the board
REF_BUF: U2.6 (-), U2.7; also elsewhere on the board

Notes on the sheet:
J_BP: 5V_SYS (piny 10/12) zasila plytke. 3V3_IO (J_BP.14) idzie tylko na kolek J_SV2. Logika pracuje z lokalnego 3V3_P06.
D1: anoda 3V3_P06, katoda 5VA_P06. Budzet MEASURE: 180 mA, wiekszosc poboru przez R21 obciazajacy styk. R6 1R/1W lezacy; C3 220u (1.10): impuls ladowania ok. 3 mJ.
P06-R2 / 01 ZASILANIE LOKALNE

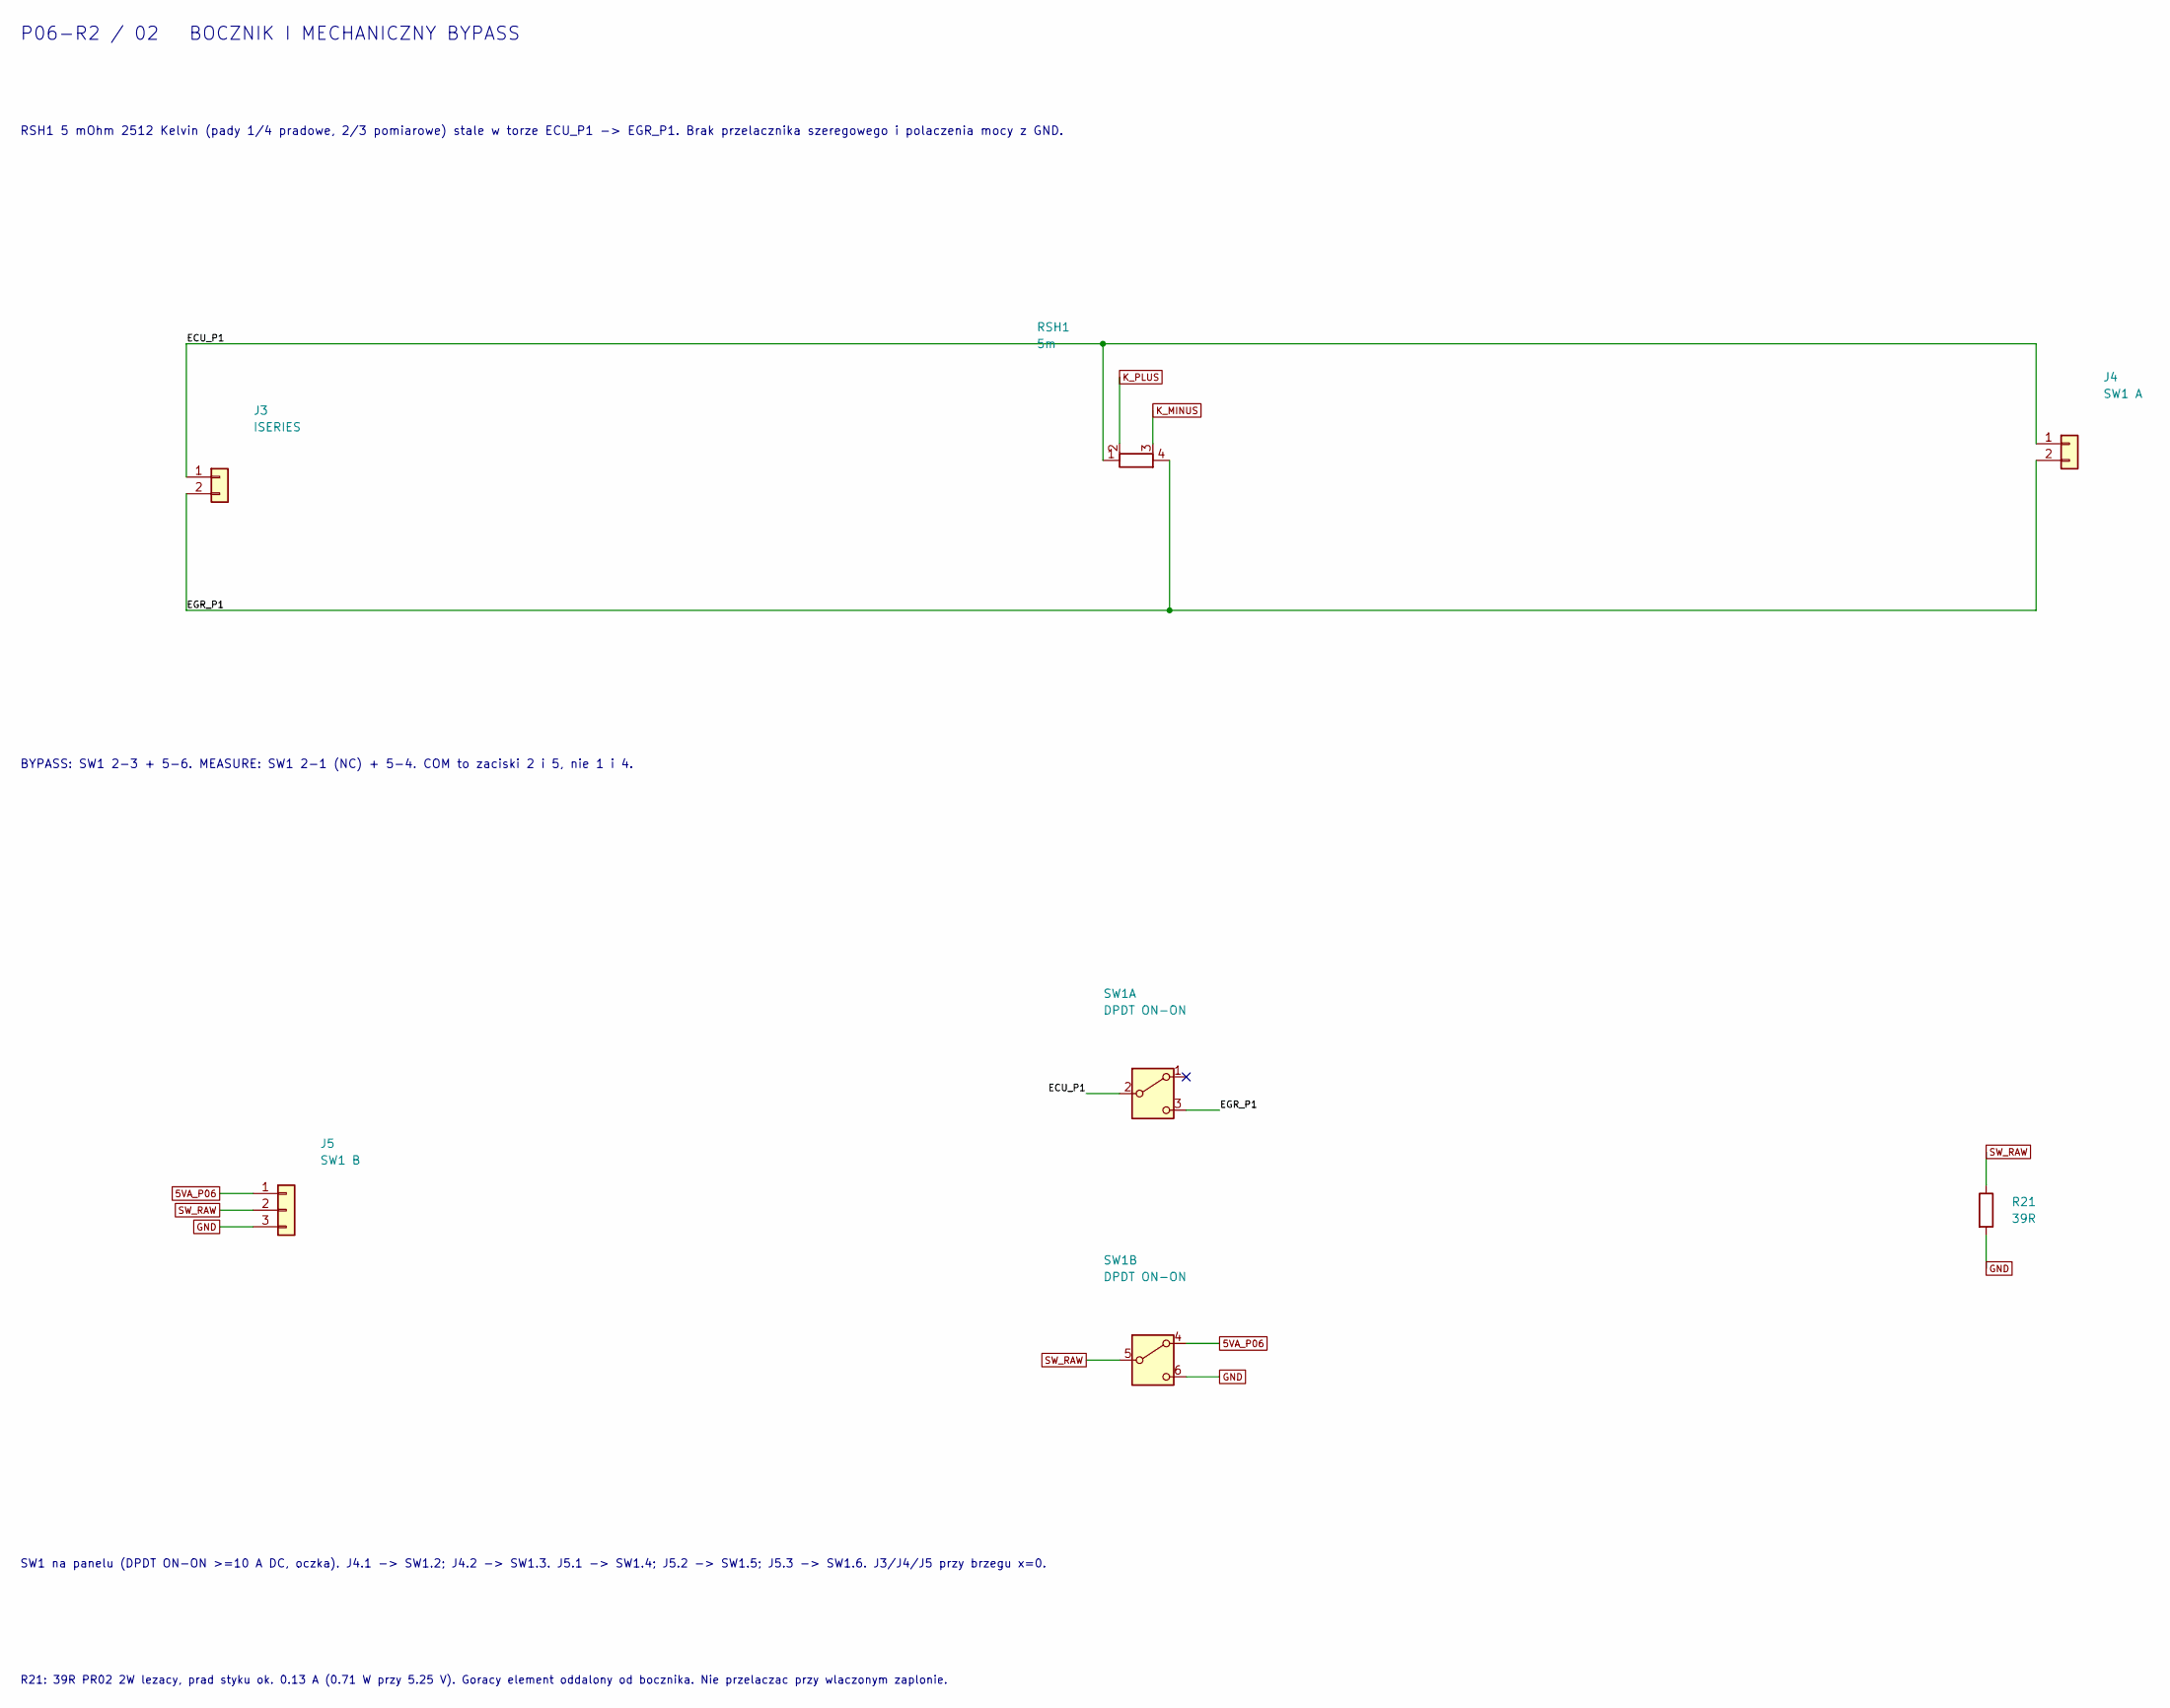
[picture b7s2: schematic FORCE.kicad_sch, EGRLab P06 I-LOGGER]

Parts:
J3: ISERIES; PTH_ISERIES; MPN Soldered harness
J4: SW1 A; PTH_BYPASS; MPN Soldered harness
J5: SW1 B; PTH_SWSTATUS; MPN Soldered harness
R21: 39R; R_PR02_P17.78; MPN PR02000203909JA100 (Vishay PR02 39R 5% 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
RSH1: 5m; R_Shunt_Vishay_WSK2512_T1.19mm_SenseE1.70; MPN WSK25125L000FEA (Vishay WSK2512, 5 mOhm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
SW1: DPDT ON-ON; OFFBOARD; MPN DPDT ON-ON panel toggle >=10A 12-30VDC,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

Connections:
5VA_P06: J5.1, SW1.4 (A); also elsewhere on the board
/FORCE/ECU_P1: J3.1, J4.1, RSH1.1, SW1.2 (B)
/FORCE/EGR_P1: J3.2, J4.2, RSH1.4, SW1.3 (C)
GND: J5.3, R21.2, SW1.6 (C); also elsewhere on the board
K_MINUS: RSH1.3; also elsewhere on the board
K_PLUS: RSH1.2; also elsewhere on the board
SW_RAW: J5.2, R21.1, SW1.5 (B); also elsewhere on the board

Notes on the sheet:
RSH1 5 mOhm 2512 Kelvin (pady 1/4 pradowe, 2/3 pomiarowe) stale w torze ECU_P1 -> EGR_P1. Brak przelacznika szeregowego i polaczenia mocy z GND.
BYPASS: SW1 2-3 + 5-6. MEASURE: SW1 2-1 (NC) + 5-4. COM to zaciski 2 i 5, nie 1 i 4.
SW1 na panelu (DPDT ON-ON >=10 A DC, oczka). J4.1 -> SW1.2; J4.2 -> SW1.3. J5.1 -> SW1.4; J5.2 -> SW1.5; J5.3 -> SW1.6. J3/J4/J5 przy brzegu x=0.
R21: 39R PR02 2W lezacy, prad styku ok. 0.13 A (0.71 W przy 5.25 V). Goracy element oddalony od bocznika. Nie przelaczac przy wlaczonym zaplonie.
P06-R2 / 02 BOCZNIK I MECHANICZNY BYPASS
